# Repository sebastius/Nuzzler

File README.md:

# Nuzzler
A hotend heater for Bambu Lab X1C hotends: heat a nozzle to a controlled temperature so it can be cleaned (cold pull, purge, needle).

> **v2 is untested.** The design passes ERC and DRC (including schematic parity), but no board has been built yet.

## v2: power/driver board for a Cheap Yellow Display

v1 was an Arduino Nano with a display module on a 12V USB-C PD trigger. v2 drops the Nano and display. It is now a
power and heater-driver board with a 6-pin header to a **Cheap Yellow Display** (ESP32-2432S028), which will do the UI and control.

What changed and why:

| | v1 | v2 |
|---|---|---|
| Supply | 12V PD (12 W at 12 Ω) | **20V PD (≈33 W, 1.7 A)** |
| 5V rail | Nano regulator (fed from VIN) | **XL1509-5.0 buck** (4.5–40 V in, JLC basic part) |
| MOSFET | IRF540N (not logic level, driven at ~4.5 V) | **IRLZ44N**, gate driven to 5 V by an LM393 comparator (HEAT > 2.5 V), so a 3.3 V ESP32 pin can switch it fully |
| Thermistor pull-up | 100k to 5V (≈5–10 °C per ADC step at 220 °C) | **2k2 to the CYD 3.3V**: good resolution from 90 to 290 °C and never above 3.3 V on the ESP32 ADC |
| Protection | none | 2.5A PTC, SMF24A TVS, 100 µF bulk, **hardware over-temperature cutoff** (other half of the LM393, trips at ~281 °C, re-enables at ~270 °C; wired-AND on the gate) |
| Extras | | Supply-voltage sense (VSENSE), LEDs for 5V / heater on |

### X1C hotend facts (used for the design)
- Ceramic heater: 48 W, ~12 Ω cold, rated for 300 °C. At 24 V in the printer that gives 48 W; at 20 V here ≈33 W.
- Thermistor: NTC, 50–100 kΩ at room temperature (almost certainly 100k, B≈3950).
- Cold pull: heat to ~220 °C (PLA), then let it cool to ~90–100 °C and pull.

### Header J4 → CYD

| J4 | Signal | CYD |
|---|---|---|
| 1 | 5V (through Schottky D4) | P1 VIN |
| 2 | NTC (thermistor, 0–3.3 V) | P3 IO35 (ADC1, input only) |
| 3 | HTR (heater enable / PWM, 3.3 V logic) | CN1 IO22 (or IO27) |
| 4 | VS (supply voltage /9.33: 20 V → 2.14 V) | IO34 after removing the LDR (optional) |
| 5 | 3V3 (from the CYD: thermistor pull-up and comparator reference) | CN1 3.3V |
| 6 | GND | P1 GND |

The heater can't turn on without the CYD: HTR has a pulldown, and without 3V3 the thermistor reads "cold" but HTR stays low.

### Firmware notes
- Thermistor: `R_ntc = 2200 * V / (3.3 - V)`, then Beta or Steinhart–Hart. Use the ESP32 ADC calibration (11 dB attenuation).
- At 20 V the hotend heats quickly and overshoots without a fan: use PID, a soft maximum of ~260 °C (the hardware cutoff is at ~281 °C, the heater rating is 300 °C) and thermal-runaway detection (no temperature rise within X s while heating → off).
- PWM: anything up to ~1 kHz is fine; a slow PWM (e.g. 10 Hz) also works for a heater.
- If VS is used: refuse to heat unless the PD trigger actually delivers ~20 V.
- The hardware cutoff is a backstop only and does not replace firmware limits.

### Manufacturing at JLCPCB (Economic PCBA)

All SMD parts on the top side are **JLC Basic or Preferred Extended** parts, so there are **no $3.07 feeder-loading fees**.
Files are in [`jlc/`](jlc): Gerbers, `nuzzler-v2-BOM-JLC.csv` and `nuzzler-v2-CPL-JLC.csv` (top side, positions from KiCad).
Check the part rotations in JLC's placement preview (especially U1/U2 SOIC-8 and the diodes D1, D4, D5 and LEDs D2, D3).

JLC places (24 parts, 16 unique, 60 joints per board):

| Ref | Qty | Value | Footprint | LCSC | Type |
|---|---|---|---|---|---|
| U1 | 1 | XL1509-5.0E1 | SOIC-8 | C61063 | Basic |
| U2 | 1 | LM393DR2G | SOIC-8 | C7955 | Basic |
| D1 | 1 | SMF24A (TVS) | SOD-123FL | C19077514 | Preferred |
| D4 | 1 | B5819W | SOD-123 | C8598 | Basic |
| D5 | 1 | SS34 | SMA | C8678 | Basic |
| D2 | 1 | LED green | 0805 | C2297 | Basic |
| D3 | 1 | LED yellow | 0805 | C2296 | Basic |
| C2 | 1 | 10µF 50V | 1206 | C13585 | Basic |
| C3 | 1 | 10µF 25V | 0805 | C15850 | Basic |
| C5, C6, C7 | 3 | 100nF 50V | 0805 | C49678 | Basic |
| R1, R3 | 2 | 1k | 0805 | C17513 | Basic |
| R7 | 1 | 2k2 | 0805 | C17520 | Basic |
| R4, R5, R6, R9 | 4 | 10k | 0805 | C17414 | Basic |
| R13 | 1 | 12k | 0805 | C17444 | Basic |
| R2, R8, R12 | 3 | 100k | 0805 | C149504 | Basic |
| R10 | 1 | 1M | 0805 | C17514 | Basic |

Hand-soldered (through-hole, plus the small JST-GH, which is not in JLC's cheap library):

| Ref | Qty | Part | Notes |
|---|---|---|---|
| Q1 | 1 | IRLZ44N | TO-220 |
| L1 | 1 | 68µH ≥1A radial, 5 mm pitch, Ø≤8.7 mm | e.g. Fastron 07HCP-680K, Bourns RLB0914-680KL |
| C1 | 1 | 100µF 35V radial Ø6.3 mm, 2.5 mm pitch | |
| C4 | 1 | 220µF 16V radial Ø6.3 mm, 2.5 mm pitch | buck output |
| F1 | 1 | PTC Ihold 2.5A, ≥30V, radial 5.1 mm | e.g. Bourns MF-R250, Littelfuse 30R250UU |
| J1 | 1 | 1x4 pin header 2.54 mm | + USB-C PD trigger module set to 20V; check the module pinout: pins 1–2 V+, 3–4 GND |
| J2 | 1 | JST XH 2-pin horizontal (S2B-XH-A) | heater |
| J3 | 1 | JST GH 2-pin SMD horizontal (SM02B-GHS-TB) | thermistor |
| J4 | 1 | 1x6 pin header 2.54 mm | to CYD |

Board: 56 × 52 mm, 2 layers, 4× M3, all SMD on top. Gerbers and drill files: [`grbrs/nuzzler-v2-gerbers.zip`](grbrs/nuzzler-v2-gerbers.zip).

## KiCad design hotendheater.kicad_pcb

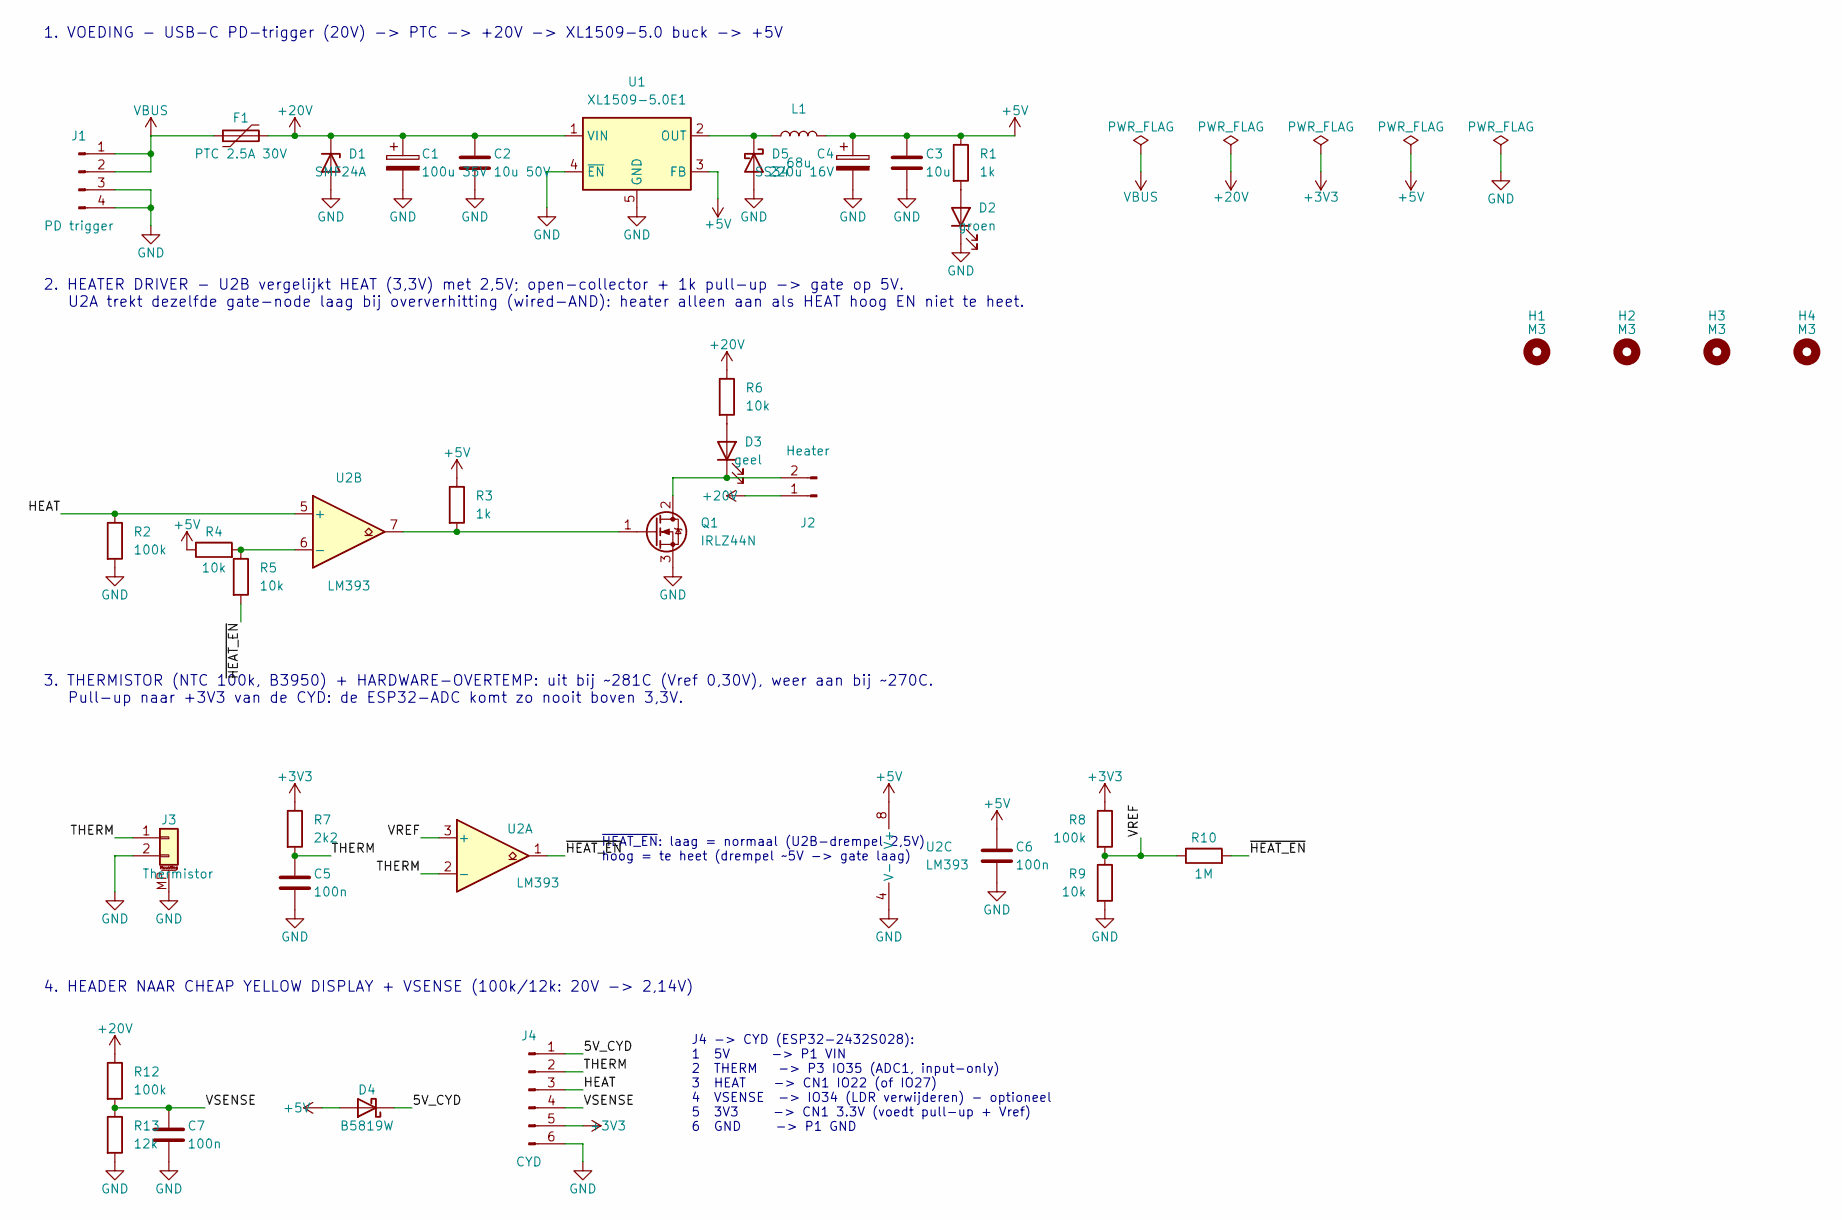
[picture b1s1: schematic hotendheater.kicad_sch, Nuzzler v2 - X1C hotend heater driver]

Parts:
C1: 100u 35V; CP_Radial_D6.3mm_P2.50mm
C2: 10u 50V; C_1206_3216Metric; LCSC C13585
C3: 10u; C_0805_2012Metric; LCSC C15850
C4: 220u 16V; CP_Radial_D6.3mm_P2.50mm
C5, C6, C7: 100n; C_0805_2012Metric; LCSC C49678
D1: SMF24A; D_SMF; LCSC C19077514
D2: groen; LED_0805_2012Metric; LCSC C2297
D3: geel; LED_0805_2012Metric; LCSC C2296
D4: B5819W; D_SOD-123; LCSC C8598
D5: SS34; D_SMA; LCSC C8678
F1: PTC 2.5A 30V; Fuse_Bourns_MF-RG300
H1, H2, H3, H4: M3; MountingHole_3.2mm_M3
J1: PD trigger; PinHeader_1x04_P2.54mm_Vertical
J2: Heater; JST_XH_S2B-XH-A_1x02_P2.50mm_Horizontal
J3: Thermistor; JST_GH_SM02B-GHS-TB_1x02-1MP_P1.25mm_Horizontal
J4: CYD; PinHeader_1x06_P2.54mm_Vertical
L1: 68u; L_Radial_D8.7mm_P5.00mm_Fastron_07HCP
Q1: IRLZ44N; TO-220-3_Vertical
R1, R3: 1k; R_0805_2012Metric; LCSC C17513
R2, R8, R12: 100k; R_0805_2012Metric; LCSC C149504
R4, R5, R6, R9: 10k; R_0805_2012Metric; LCSC C17414
R7: 2k2; R_0805_2012Metric; LCSC C17520
R10: 1M; R_0805_2012Metric; LCSC C17514
R13: 12k; R_0805_2012Metric; LCSC C17444
U1: XL1509-5.0E1; SOIC-8_3.9x4.9mm_P1.27mm; LCSC C61063
U2: LM393; SOIC-8_3.9x4.9mm_P1.27mm; LCSC C7955

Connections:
+3V3: J4.5, R7.1, R8.1
+5V: C3.1, C4.1, C6.1, D4.2 (A), L1.2, R1.1, R3.1, R4.1, U1.3 (FB), U2.8 (V+)
+20V: C1.1, C2.1, D1.1 (K), F1.2, J2.1, R6.1, R12.1, U1.1 (VIN)
/5V_CYD: D4.1 (K), J4.1
/HEAT: J4.3, R2.1, U2.5 (+)
/THERM: C5.1, J3.1, J4.2, R7.2, U2.2 (-)
/VREF: R8.2, R9.1, R10.1, U2.3 (+)
/VSENSE: C7.1, J4.4, R12.2, R13.1
/~HEAT_EN: R5.2, R10.2, U2.1
GND: C1.2, C2.2, C3.2, C4.2, C5.2, C6.2, C7.2, D1.2 (A), D2.1 (K), D5.2 (A), J1.3, J1.4, J3.2, J3.MP (MountPin), J4.6, Q1.3 (S), R2.2, R9.2, R13.2, U1.4 (~EN), U1.5 (GND), U1.6 (GND), U1.7 (GND), U1.8 (GND), U2.4 (V-)
unnamed: D2.2 (A), R1.2
unnamed: D3.2 (A), R6.2
unnamed: D3.1 (K), J2.2, Q1.2 (D)
unnamed: D5.1 (K), L1.1, U1.2 (OUT)
unnamed: Q1.1 (G), R3.2, U2.7
unnamed: R4.2, R5.1, U2.6 (-)
VBUS: F1.1, J1.1, J1.2

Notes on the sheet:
1. VOEDING - USB-C PD-trigger (20V) -> PTC -> +20V -> XL1509-5.0 buck -> +5V
2. HEATER DRIVER - U2B vergelijkt HEAT (3,3V) met 2,5V; open-collector + 1k pull-up -> gate op 5V. U2A trekt dezelfde gate-node laag bij oververhitting (wired-AND): heater alleen aan als HEAT hoog EN niet te heet.
3. THERMISTOR (NTC 100k, B3950) + HARDWARE-OVERTEMP: uit bij ~281C (Vref 0,30V), weer aan bij ~270C. Pull-up naar +3V3 van de CYD: de ESP32-ADC komt zo nooit boven 3,3V.
~{HEAT_EN}: laag = normaal (U2B-drempel 2,5V) hoog = te heet (drempel ~5V -> gate laag)
4. HEADER NAAR CHEAP YELLOW DISPLAY + VSENSE (100k/12k: 20V -> 2,14V)
J4 -> CYD (ESP32-2432S028): 1 5V -> P1 VIN 2 THERM -> P3 IO35 (ADC1, input-only) 3 HEAT -> CN1 IO22 (of IO27) 4 VSENSE -> IO34 (LDR verwijderen) - optioneel 5 3V3 -> CN1 3.3V (voedt pull-up + Vref) 6 GND -> P1 GND

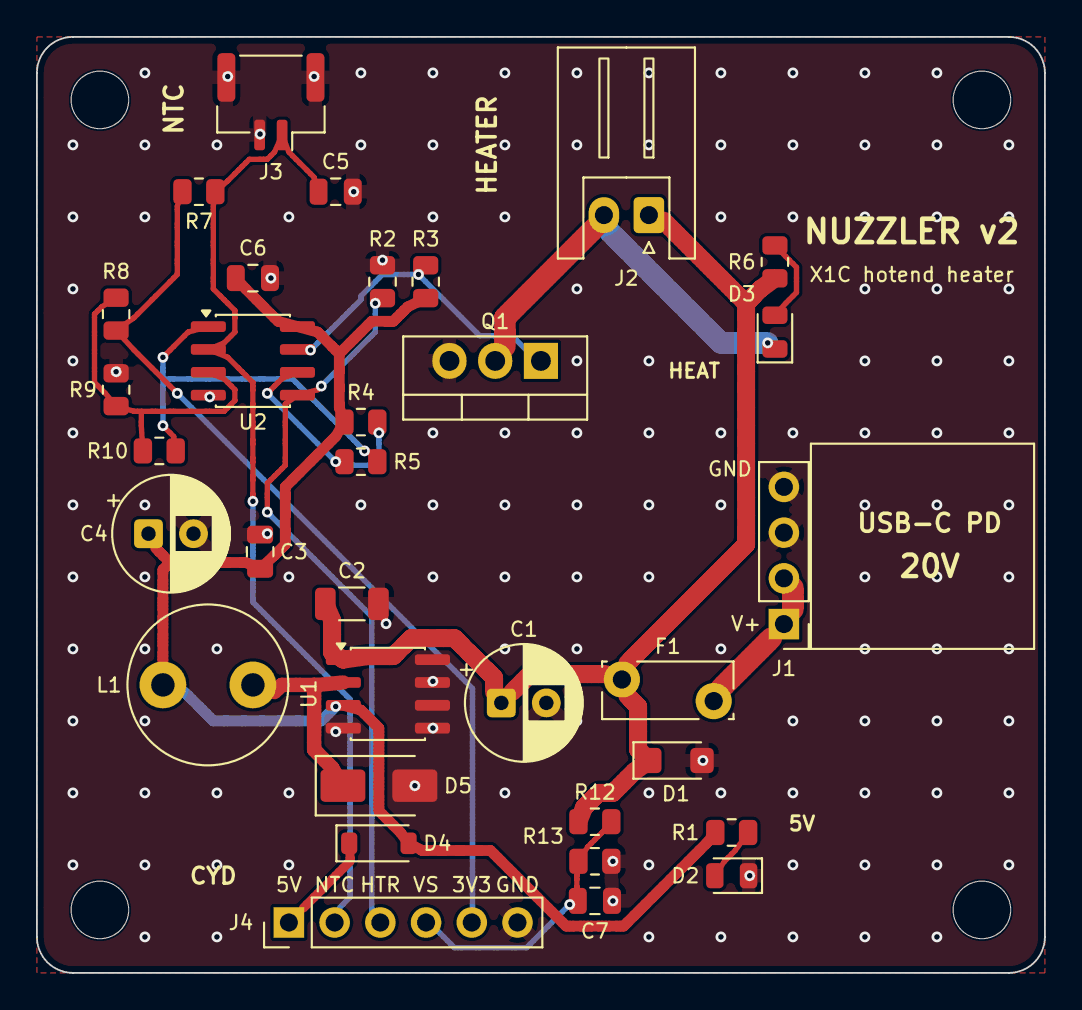
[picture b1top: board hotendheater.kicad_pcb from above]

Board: 2 copper layers, 56.0 x 52.0 mm, 37 parts (0 on the bottom side), 17 nets.

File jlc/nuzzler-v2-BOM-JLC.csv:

Comment,Designator,Footprint,LCSC Part #
10u 50V,C2,C_1206_3216Metric,C13585
10u,C3,C_0805_2012Metric,C15850
100n,"C5,C6,C7",C_0805_2012Metric,C49678
SMF24A,D1,D_SMF,C19077514
groen,D2,LED_0805_2012Metric,C2297
geel,D3,LED_0805_2012Metric,C2296
B5819W,D4,D_SOD-123,C8598
SS34,D5,D_SMA,C8678
1k,"R1,R3",R_0805_2012Metric,C17513
100k,"R2,R8,R12",R_0805_2012Metric,C149504
10k,"R4,R5,R6,R9",R_0805_2012Metric,C17414
2k2,R7,R_0805_2012Metric,C17520
1M,R10,R_0805_2012Metric,C17514
12k,R13,R_0805_2012Metric,C17444
XL1509-5.0E1,U1,SOIC-8_3.9x4.9mm_P1.27mm,C61063
LM393,U2,SOIC-8_3.9x4.9mm_P1.27mm,C7955

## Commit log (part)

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2024-11-29 Add files via upload
    Testversion. Do not make these yourself.
2024-11-29 Improvements
